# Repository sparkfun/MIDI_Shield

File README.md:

SparkFun MIDI Shield
====================

[*SparkFun MIDI Shield (DEV-12898)*](https://www.sparkfun.com/products/12898)

The MIDI Shield gives your Arduino access to the MIDI communication protocol, so you can control synthesizers, sequencers, and other musical devices.

Repository Contents
-------------------

* **/Firmware** - Example Arduino .ino sketch
* **/Hardware** - All Eagle design files (.brd, .sch)
* **/Production** - Production panel files (.brd)

Documentation
--------------
* **[Hookup Guide](https://learn.sparkfun.com/tutorials/midi-shield-hookup-guide?_ga=1.24780723.863167751.1453149924)** - Basic hookup guide for the MIDI Shield.
* **[SparkFun Fritzing repo](https://github.com/sparkfun/Fritzing_Parts)** - Fritzing diagrams for SparkFun products.
* **[SparkFun 3D Model repo](https://github.com/sparkfun/3D_Models)** - 3D models of SparkFun products. 
* **[SparkFun Graphical Datasheets](https://github.com/sparkfun/Graphical_Datasheets)** -Graphical Datasheets for various SparkFun products.

Product Versions
----------------
* [DEV-12898](https://www.sparkfun.com/products/12898)- Version 1.5. R3 compatible. Currently live. 
* [DEV-09595](https://www.sparkfun.com/products/retired/9595)- Version 1.3. Retired. 

Version History
---------------
* [V_1.5](https://github.com/sparkfun/MIDI_Shield/tree/V_1.5) - GitHub snapshot at V_1.5. 
* [V_1.3](https://github.com/sparkfun/MIDI_Shield/tree/v1.3) - GitHub snapshot at V_1.3

License Information
-------------------

This product is _**open source**_! 

Please review the LICENSE.md file for license information. 

If you have any questions or concerns on licensing, please contact techsupport@sparkfun.com.

Distributed as-is; no warranty is given.

\- Your friends at SparkFun.

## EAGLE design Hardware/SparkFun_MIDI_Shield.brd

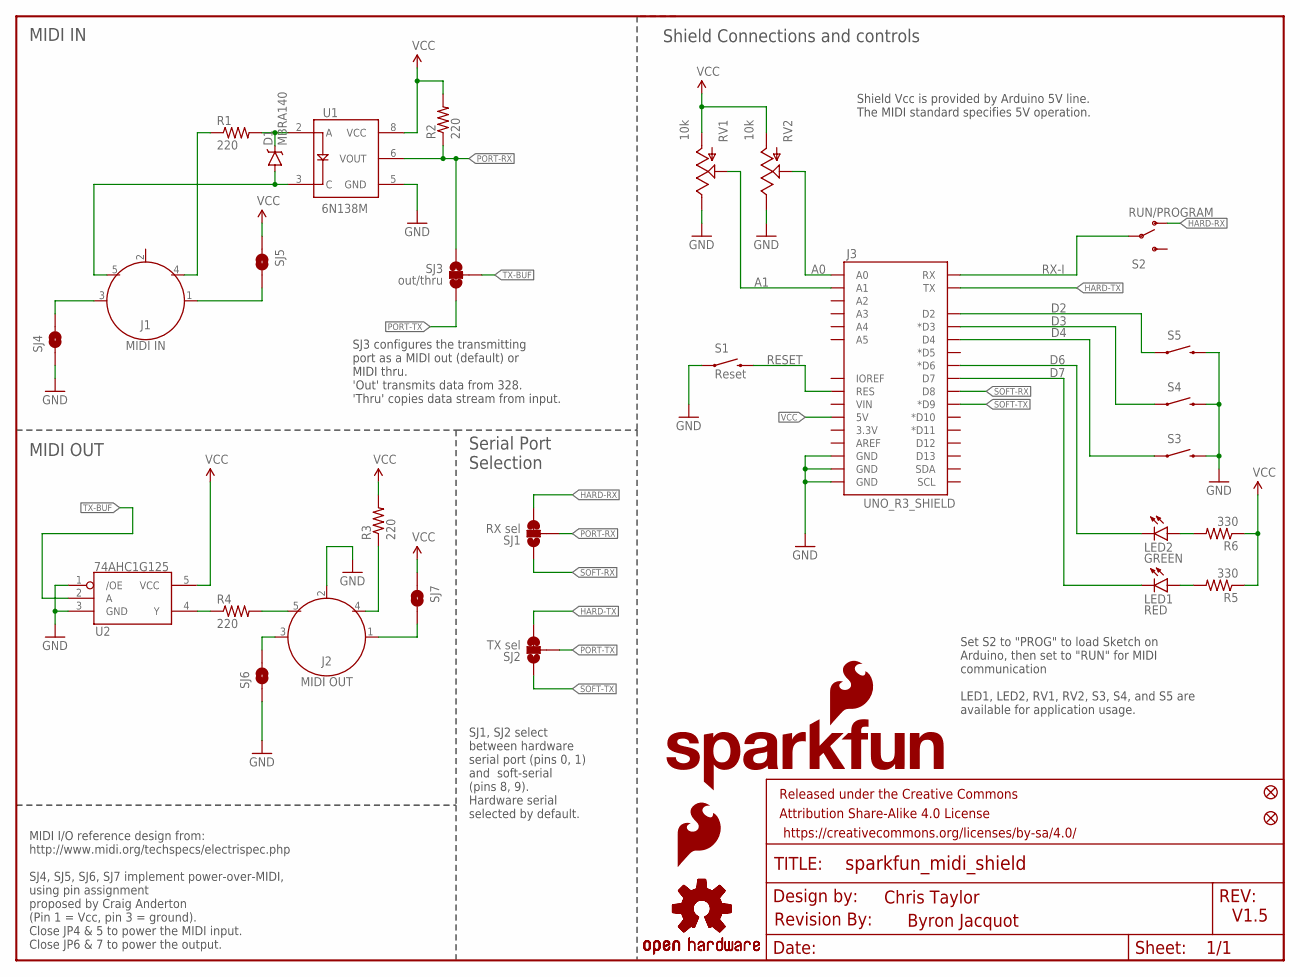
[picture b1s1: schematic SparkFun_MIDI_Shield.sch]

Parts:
D1: MBRA140; SMA-DIODE
FID1, FID2: FIDUCIALUFIDUCIAL; MICRO-FIDUCIAL
FRAME1: Frame; CREATIVE_COMMONS
J1: MIDI IN; 5-PIN-DIN-RA-PCB-NEW
J2: MIDI OUT; 5-PIN-DIN-RA-PCB-NEW
J3: UNO_R3_SHIELD
LED1: RED; LED-0603
LED2: GREEN; LED-0603
LOGO1: SFE_LOGO_NAME_FLAME.2_INCH; SFE_LOGO_NAME_FLAME_.2
LOGO2: OSHW-LOGOS; OSHW-LOGO-S
LOGO3: OSHW-LOGOM; OSHW-LOGO-M
LOGO5: SFE_LOGO_FLAME.1_INCH; SFE_LOGO_FLAME_.1
R1, R2, R3, R4: 220; 0603-RES
R5, R6: 330; 0603-RES
RV1, RV2: 10k; ALPS_POT
S1: Reset; TACTILE-SWITCH-SMD
S2: RUN/PROGRAM; AYZ0202
S3, S4, S5: SWITCH-MOMENTARY-212MM; TACTILE-PTH-12MM
SJ1: RX sel; PAD-JUMPER-3-2OF3_NC_BY_TRACE_YES_SILK_FULL_BOX
SJ2: TX sel; PAD-JUMPER-3-2OF3_NC_BY_TRACE_YES_SILK_FULL_BOX
SJ3: out/thru; PAD-JUMPER-3-2OF3_NC_BY_TRACE_YES_SILK_FULL_BOX
SJ4, SJ5, SJ6, SJ7: JUMPER-PAD-2-NOYES_SILK; PAD-JUMPER-2-NO_YES_SILK
U1: 6N138M; 8-SMD
U2: 74AHC1G125; SOT23-5
U$1: REVISION

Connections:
56: D1.C, R1.2, U1.2 (A)
1235: J2.4, R3.1
A0: J3.A0, RV2.P$2 (S)
A1: J3.A1, RV1.P$2 (S)
D2: J3.D2, S5.1
D3: J3.D3 (*D3), S4.1
D4: J3.D4, S3.1
D6: J3.D6 (*D6), LED2.C
D7: J3.D7, LED1.C
GND: J2.2, J3.GND@0 (GND), J3.GND@1 (GND), J3.GND@2 (GND), RV1.P$1 (E), RV2.P$1 (E), S1.1, S3.3 (2), S4.3 (2), S5.3 (2), SJ4.1, SJ6.1, U1.5 (GND), U2.1 (/OE), U2.3 (GND)
HARD-RX: S2.1 (O), SJ1.3
HARD-TX: J3.TX, SJ2.3
unnamed: J2.5, R4.2
unnamed: J1.4, R1.1
unnamed: R4.1, U2.4 (Y)
unnamed: J2.3, SJ6.2
unnamed: J2.1, SJ7.2
unnamed: J1.3, SJ4.2
unnamed: J1.1, SJ5.2
unnamed: LED1.A, R5.2
unnamed: LED2.A, R6.2
PIN5: D1.A, J1.5, U1.3 (C)
PORT-RX: R2.1, SJ1.2, SJ3.1, U1.6 (VOUT)
PORT-TX: SJ2.2, SJ3.3
RESET: J3.RES, S1.3 (2)
RX-I: J3.RX, S2.2
SOFT-RX: J3.D8, SJ1.1
SOFT-TX: J3.D9 (*D9), SJ2.1
TX-BUF: SJ3.2, U2.2 (A)
VCC: J3.5V, R2.2, R3.2, R5.1, R6.1, RV1.P$3 (A), RV2.P$3 (A), SJ5.1, SJ7.1, U1.8 (VCC), U2.5 (VCC)

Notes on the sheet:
MIDI IN
MIDI OUT
Byron Jacquot
V1.5
Shield Connections and controls
MIDI I/O reference design from: http://www.midi.org/techspecs/electrispec.php SJ4, SJ5, SJ6, SJ7 implement power-over-MIDI, using pin assignment proposed by Craig Anderton (Pin 1 = Vcc, pin 3 = ground). Close JP4 & 5 to power the MIDI input. Close JP6 & 7 to power the output.
Set S2 to "PROG" to load Sketch on Arduino, then set to "RUN" for MIDI communication LED1, LED2, RV1, RV2, S3, S4, and S5 are available for application usage.
Serial Port Selection
SJ1, SJ2 select between hardware serial port (pins 0, 1) and soft-serial (pins 8, 9). Hardware serial selected by default.
Shield Vcc is provided by Arduino 5V line. The MIDI standard specifies 5V operation.
SJ3 configures the transmitting port as a MIDI out (default) or MIDI thru. 'Out' transmits data from 328. 'Thru' copies data stream from input.
Chris Taylor

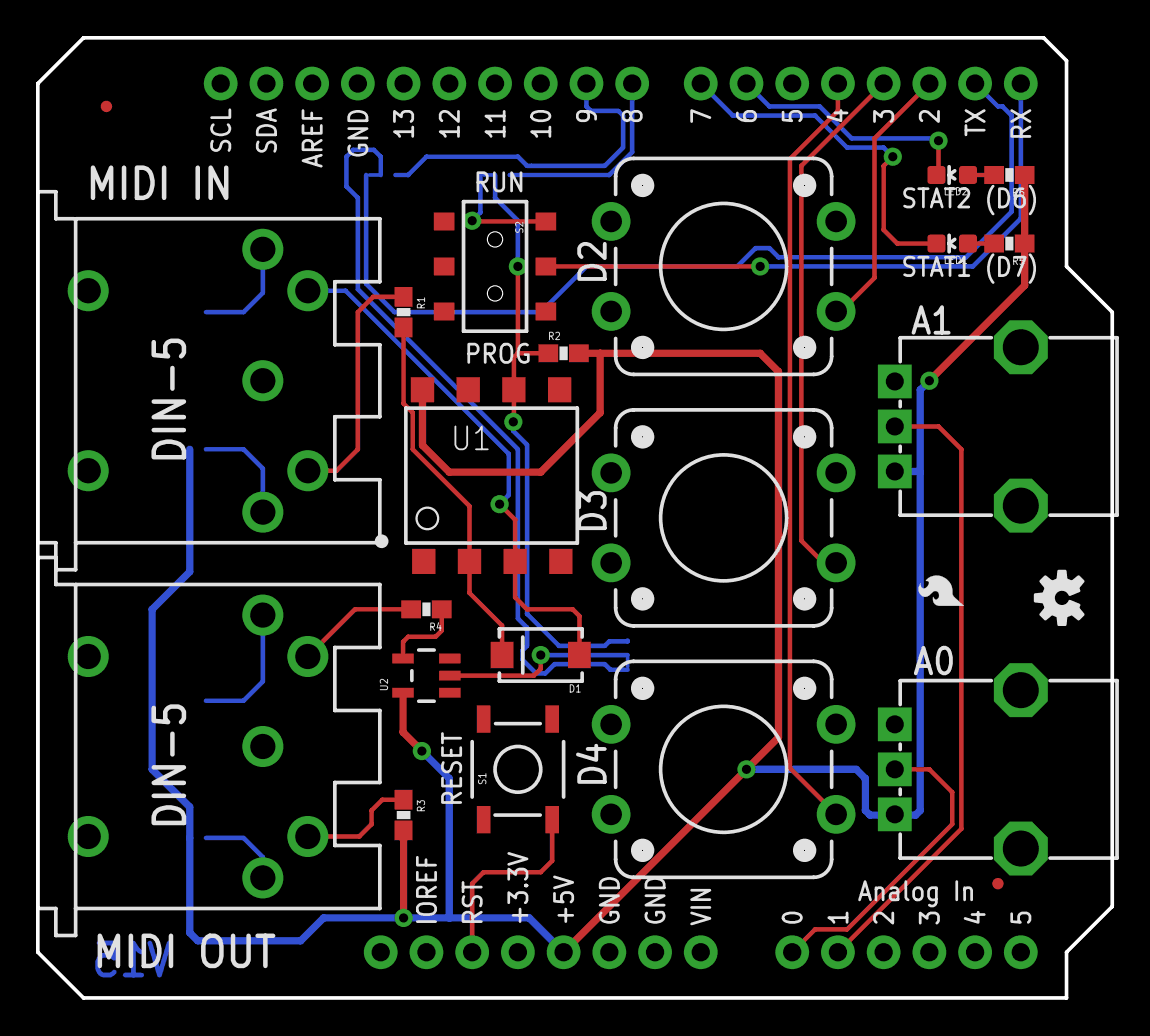
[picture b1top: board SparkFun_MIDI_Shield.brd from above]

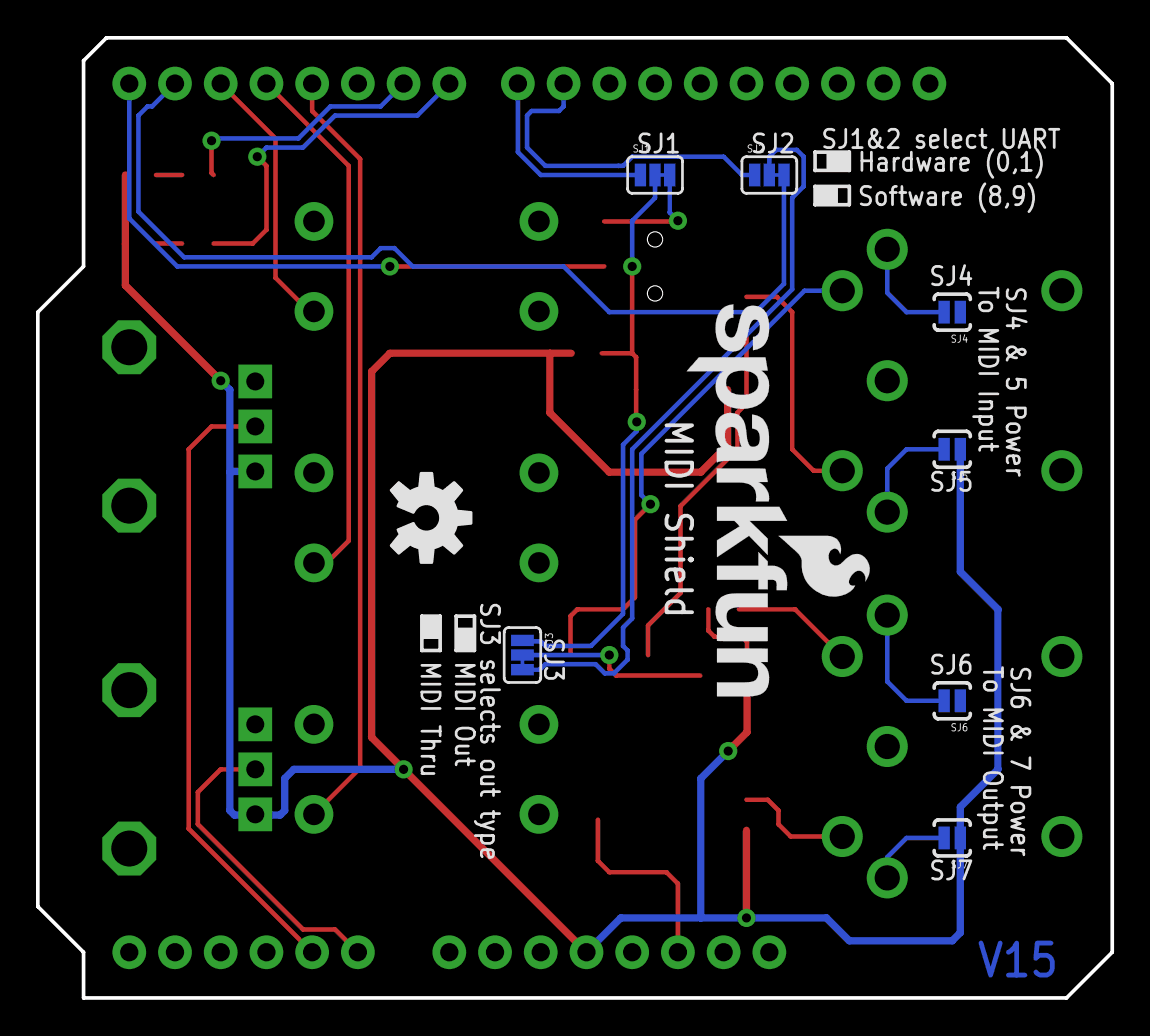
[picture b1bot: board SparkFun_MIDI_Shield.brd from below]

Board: 3 copper layers, 59.7 x 53.3 mm, 36 parts (9 on the bottom side), 30 nets.

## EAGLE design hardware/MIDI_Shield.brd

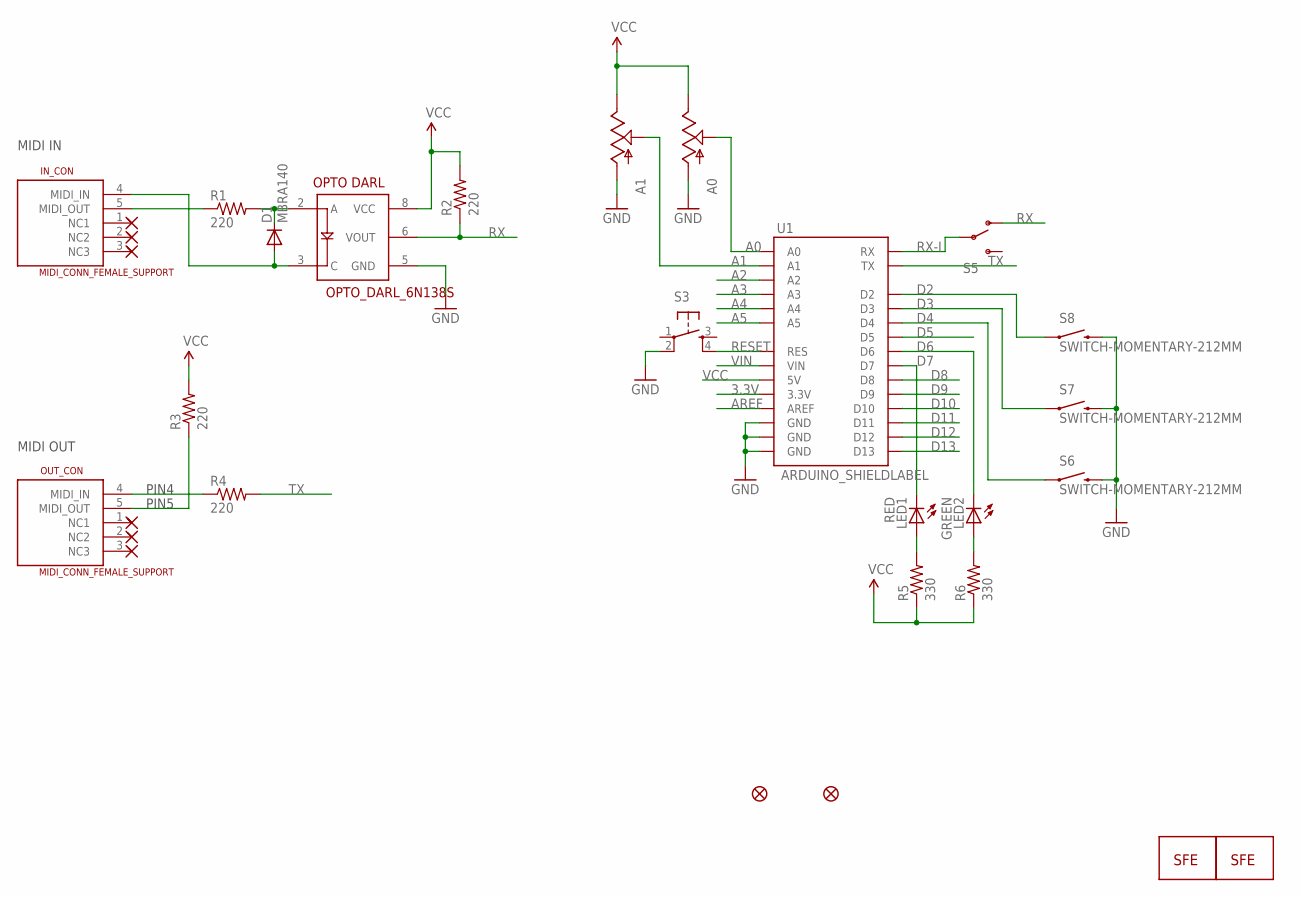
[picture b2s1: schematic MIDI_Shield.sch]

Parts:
A0, A1: POT; ALPS_POT
D1: MBRA140; SMA-DIODE
IN_CON: MIDI_CONN_FEMALE_SUPPORT; DIN_5_FEMALE_SUPPORT
JP1, JP2: FIDUCIALUFIDUCIAL; MICRO-FIDUCIAL
JP3: LOGO-SFENEW; SFE-NEW-WEBLOGO
JP4: LOGO-SFESK; SFE-LOGO-FLAME
LED1: RED; LED-0603
LED2: GREEN; LED-0603
OUT_CON: MIDI_CONN_FEMALE_SUPPORT; DIN_5_FEMALE_SUPPORT
R1, R2, R3, R4: 220; 0402-RES
R5, R6: 330; 0402-RES
S3: TAC_SWITCHSMD; TACTILE_SWITCH_SMD
S5: SWITCH-SPSTSMD; AYZ0202
S6, S7, S8: SWITCH-MOMENTARY-212MM; TACTILE-PTH-12MM
U1: ARDUINO_SHIELDLABEL; DUEMILANOVE_SHIELD
U$6: OPTO_DARL_6N138S; 8-SMD

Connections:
56: D1.C, R1.2, U$6.2 (A)
1235: OUT_CON.5 (MIDI_OUT), R3.1
A0: A0.P$2 (S), U1.A0; also elsewhere on the board
A1: A1.P$2 (S), U1.A1; also elsewhere on the board
D2: S8.1, U1.D2; also elsewhere on the board
D3: S7.1, U1.D3; also elsewhere on the board
D4: S6.1, U1.D4; also elsewhere on the board
D6: LED2.C, U1.D6; also elsewhere on the board
D7: LED1.C, U1.D7; also elsewhere on the board
GND: A0.P$3 (A), A1.P$3 (A), OUT_CON.2 (NC2), S3.2, S6.3 (2), S7.3 (2), S8.3 (2), U1.GND@0 (GND), U1.GND@1 (GND), U1.GND@2 (GND), U$6.5 (GND); also elsewhere on the board
unnamed: OUT_CON.4 (MIDI_IN), R4.1
unnamed: LED1.A, R5.2
unnamed: LED2.A, R6.2
unnamed: IN_CON.5 (MIDI_OUT), R1.1
PIN5: D1.A, IN_CON.4 (MIDI_IN), U$6.3 (C)
RX: R2.1, S5.1 (O), U$6.6 (VOUT)
RX-I: S5.2, U1.RX; also elsewhere on the board
TX: R4.2, U1.TX; also elsewhere on the board

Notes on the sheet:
PIN4
PIN5
MIDI IN
MIDI OUT

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
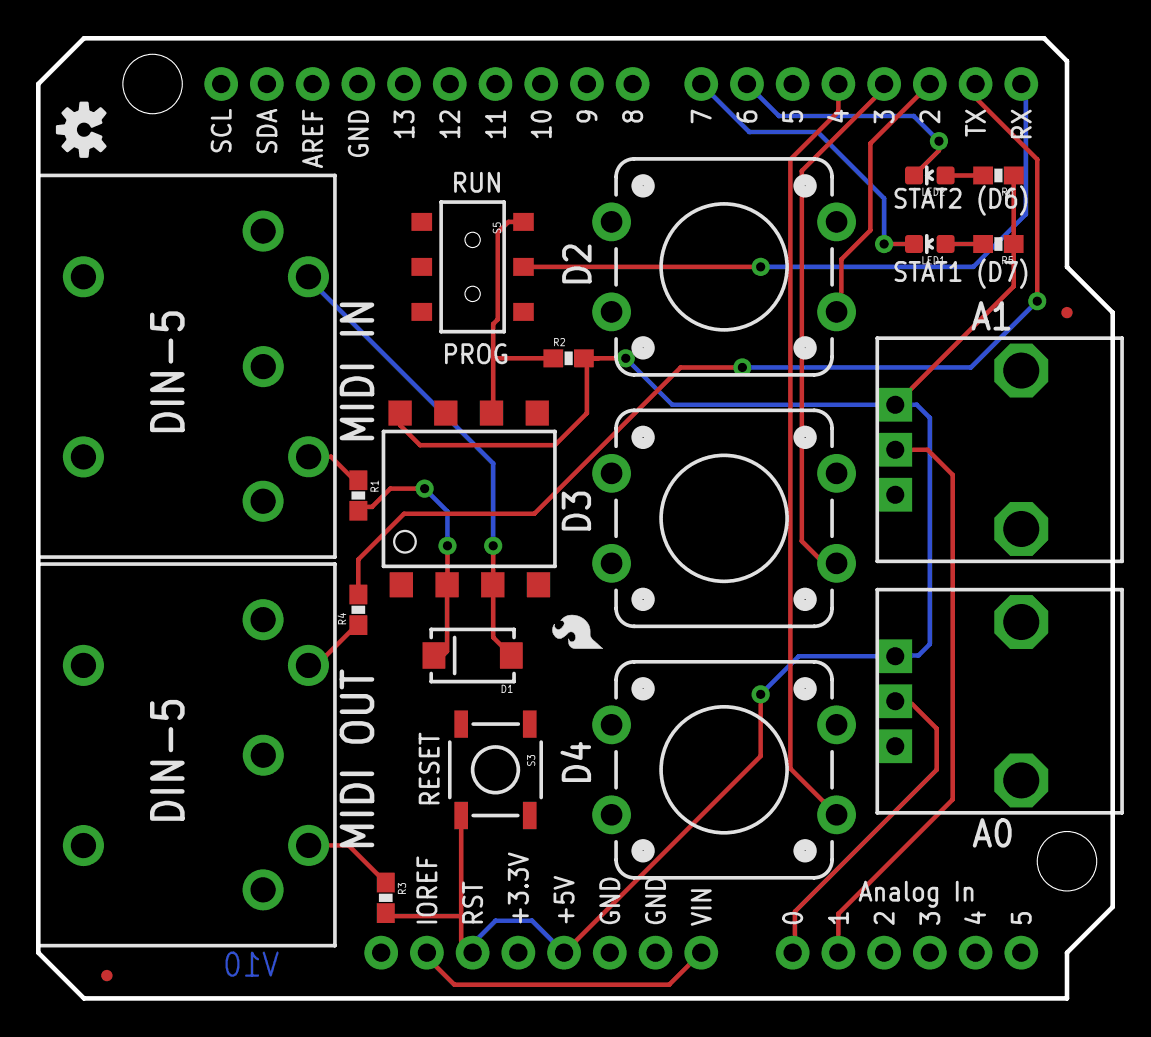
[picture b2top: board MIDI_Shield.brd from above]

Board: 2 copper layers, 59.7 x 53.3 mm, 27 parts (1 on the bottom side), 20 nets.

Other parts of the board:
U$1: ARDUINO_R3_SHIELD; UNO_R3_SHIELD
U$2, U$3: STAND-OFF
U$4: OSHW-LOGO-S

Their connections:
A0: U$1.A0; also elsewhere on the board
A1: U$1.A1; also elsewhere on the board
D2: U$1.D2; also elsewhere on the board
D3: U$1.D3; also elsewhere on the board
D4: U$1.D4; also elsewhere on the board
D6: U$1.D6; also elsewhere on the board
D7: U$1.D7; also elsewhere on the board
GND: U$1.GND@0, U$1.GND@1, U$1.GND@2; also elsewhere on the board
RX-I: U$1.RX; also elsewhere on the board
TX: U$1.TX; also elsewhere on the board
VIN: U$1.IOREF, U$1.VIN

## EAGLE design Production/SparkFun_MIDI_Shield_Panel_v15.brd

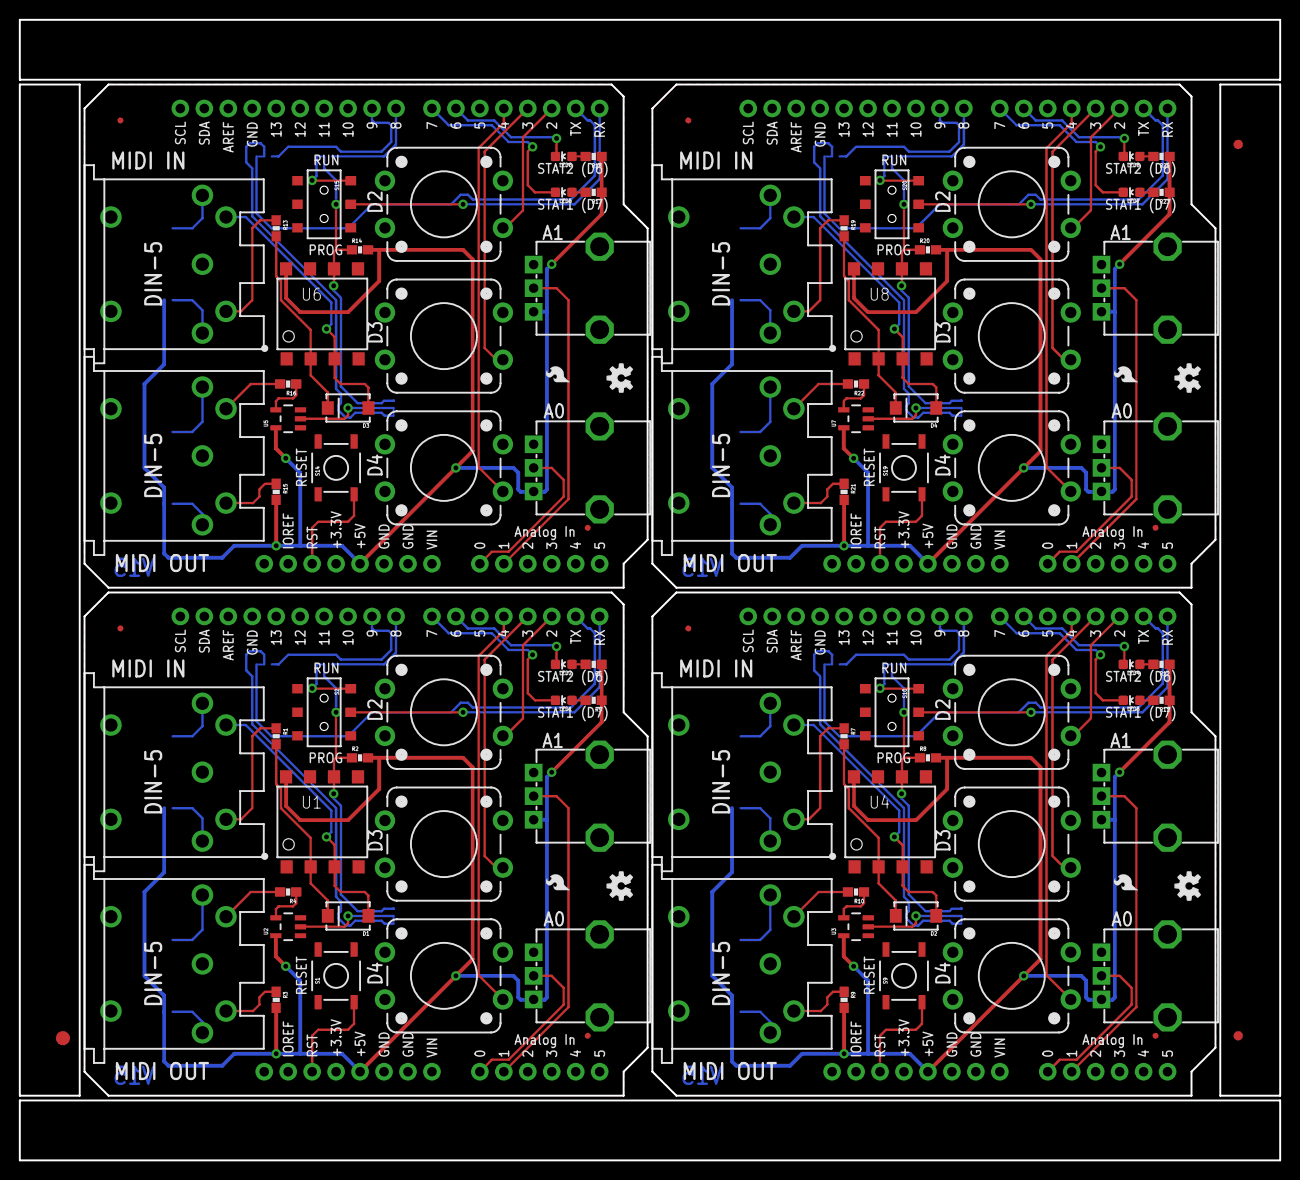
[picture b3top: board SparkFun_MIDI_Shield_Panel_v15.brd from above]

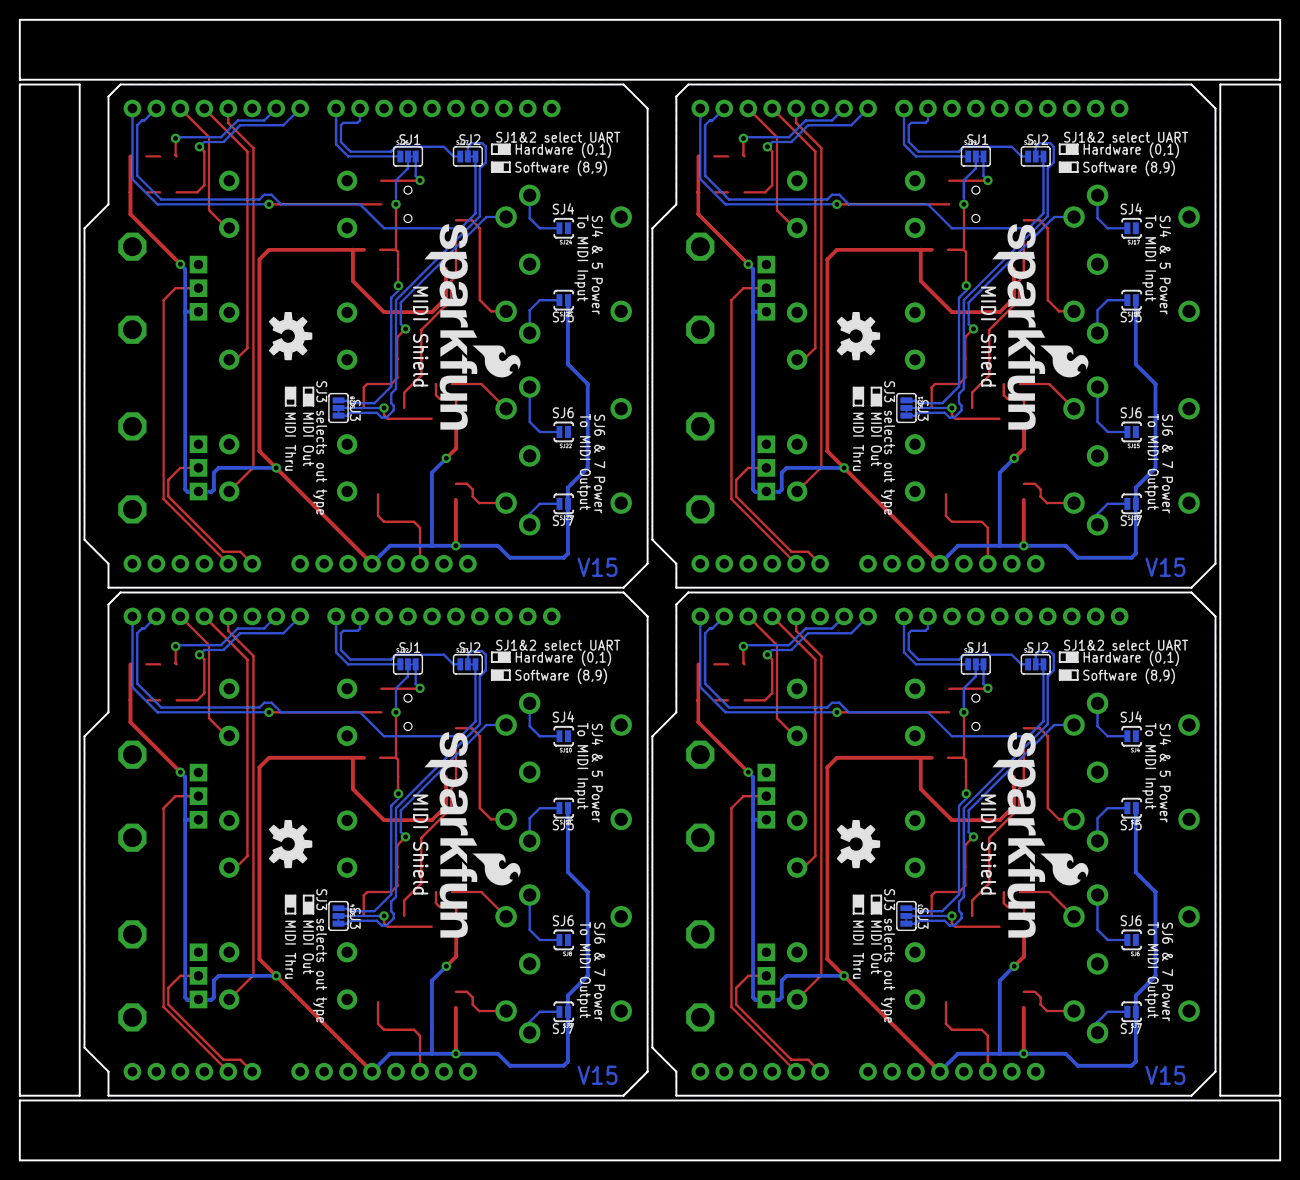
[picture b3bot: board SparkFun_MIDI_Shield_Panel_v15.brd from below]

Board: 3 copper layers, 133.6 x 120.9 mm, 139 parts (36 on the bottom side), 120 nets.

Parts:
D1, D2, D3, D4: MBRA140; SMA-DIODE
E$1: FIDUCIAL-1.5X3
E$4, E$5: FIDUCIAL-1X2
FID1, FID2, FID3, FID4, FID5, FID6, FID7, FID8: FIDUCIALUFIDUCIAL; MICRO-FIDUCIAL
J1, J4, J7, J10: MIDI IN; 5-PIN-DIN-RA-PCB-NEW
J2, J5, J8, J11: MIDI OUT; 5-PIN-DIN-RA-PCB-NEW
J3, J6, J9, J12: UNO_R3_SHIELD
LED1, LED3, LED5, LED7: RED; LED-0603
LED2, LED4, LED6, LED8: GREEN; LED-0603
LOGO1, LOGO4, LOGO9, LOGO13: SFE_LOGO_NAME_FLAME.2_INCH; SFE_LOGO_NAME_FLAME_.2
LOGO2, LOGO6, LOGO10, LOGO14: OSHW-LOGOS; OSHW-LOGO-S
LOGO3, LOGO7, LOGO11, LOGO15: OSHW-LOGOM; OSHW-LOGO-M
LOGO5, LOGO8, LOGO12, LOGO16: SFE_LOGO_FLAME.1_INCH; SFE_LOGO_FLAME_.1
R1, R2, R3, R4, R7, R8, R9, R10, R13, R14, R15, R16, R19, R20, R21, R22: 220; 0603-RES
R5, R6, R11, R12, R17, R18, R23, R24: 330; 0603-RES
RV1, RV2, RV3, RV4, RV5, RV6, RV7, RV8: 10k; ALPS_POT
S1, S9, S14, S19: Reset; TACTILE-SWITCH-SMD
S2, S10, S15, S20: RUN/PROGRAM; AYZ0202
S3, S4, S5, S6, S7, S8, S11, S12, S13, S16, S17, S18: SWITCH-MOMENTARY-212MM; TACTILE-PTH-12MM
SJ1, SJ12, SJ19, SJ26: RX sel; PAD-JUMPER-3-2OF3_NC_BY_TRACE_YES_SILK_FULL_BOX
SJ2, SJ13, SJ20, SJ27: TX sel; PAD-JUMPER-3-2OF3_NC_BY_TRACE_YES_SILK_FULL_BOX
SJ3, SJ14, SJ21, SJ28: out/thru; PAD-JUMPER-3-2OF3_NC_BY_TRACE_YES_SILK_FULL_BOX
SJ4, SJ5, SJ6, SJ7, SJ8, SJ9, SJ10, SJ11, SJ15, SJ16, SJ17, SJ18, SJ22, SJ23, SJ24, SJ25: JUMPER-PAD-2-NOYES_SILK; PAD-JUMPER-2-NO_YES_SILK
U1, U4, U6, U8: 6N138M; 8-SMD
U2, U3, U5, U7: 74AHC1G125; SOT23-5

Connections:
1: D2.C, R7.2, U4.2
2: J5.4, R9.1
3: D3.C, R13.2, U6.2
4: J8.4, R15.1
5: D4.C, R19.2, U8.2
6: J11.4, R21.1
56: D1.C, R1.2, U1.2
1235: J2.4, R3.1
A0: J3.A0, RV2.P$2
A1: J3.A1, RV1.P$2
A2: J6.A1, RV3.P$2
A3: J6.A0, RV4.P$2
A4: J9.A1, RV5.P$2
A5: J9.A0, RV6.P$2
A6: J12.A1, RV7.P$2
A7: J12.A0, RV8.P$2
D1: J6.D2, S8.1
D2: J3.D2, S5.1
D3: J3.D3, S4.1
D4: J3.D4, S3.1
D5: J6.D3, S7.1
D6: J3.D6, LED2.C
D7: J3.D7, LED1.C
D8: J6.D4, S6.1
D9: J6.D7, LED3.C
D10: J6.D6, LED4.C
D11: J9.D2, S13.1
D12: J9.D3, S12.1
D13: J9.D4, S11.1
D14: J9.D7, LED5.C
D15: J9.D6, LED6.C
D16: J12.D2, S18.1
D17: J12.D3, S17.1
D18: J12.D4, S16.1
D19: J12.D7, LED7.C
D20: J12.D6, LED8.C
GND: J2.2, J3.GND@0, J3.GND@1, J3.GND@2, RV1.P$1, RV2.P$1, S1.1, S3.3, S4.3, S5.3, SJ4.1, SJ6.1, U1.5, U2.1, U2.3
GND1: J5.2, J6.GND@0, J6.GND@1, J6.GND@2, RV3.P$1, RV4.P$1, S6.3, S7.3, S8.3, S9.1, SJ8.1, SJ10.1, U3.1, U3.3, U4.5
GND2: J8.2, J9.GND@0, J9.GND@1, J9.GND@2, RV5.P$1, RV6.P$1, S11.3, S12.3, S13.3, S14.1, SJ15.1, SJ17.1, U5.1, U5.3, U6.5
GND3: J11.2, J12.GND@0, J12.GND@1, J12.GND@2, RV7.P$1, RV8.P$1, S16.3, S17.3, S18.3, S19.1, SJ22.1, SJ24.1, U7.1, U7.3, U8.5
HARD-RX: S2.1, SJ1.3
HARD-RX1: S10.1, SJ12.3
HARD-RX2: S15.1, SJ19.3
HARD-RX3: S20.1, SJ26.3
HARD-TX: J3.TX, SJ2.3
HARD-TX1: J6.TX, SJ13.3
HARD-TX2: J9.TX, SJ20.3
HARD-TX3: J12.TX, SJ27.3
unnamed: J2.5, R4.2
unnamed: J1.4, R1.1
unnamed: R4.1, U2.4
unnamed: J2.3, SJ6.2
unnamed: J2.1, SJ7.2
unnamed: J1.3, SJ4.2
unnamed: J1.1, SJ5.2
unnamed: LED3.A, R11.2
unnamed: LED1.A, R5.2
unnamed: LED2.A, R6.2
unnamed: LED4.A, R12.2
unnamed: J4.4, R7.1
unnamed: J5.5, R10.2
unnamed: R10.1, U3.4
unnamed: J5.3, SJ8.2
unnamed: J5.1, SJ9.2
unnamed: J4.3, SJ10.2
unnamed: J4.1, SJ11.2
unnamed: LED5.A, R17.2
unnamed: LED6.A, R18.2
unnamed: J7.4, R13.1
unnamed: J8.5, R16.2
unnamed: R16.1, U5.4
unnamed: J8.3, SJ15.2
unnamed: J8.1, SJ16.2
unnamed: J7.3, SJ17.2
unnamed: J7.1, SJ18.2
unnamed: LED7.A, R23.2
unnamed: LED8.A, R24.2
unnamed: J10.4, R19.1
unnamed: J11.5, R22.2
unnamed: R22.1, U7.4
unnamed: J11.3, SJ22.2
unnamed: J11.1, SJ23.2
unnamed: J10.3, SJ24.2
unnamed: J10.1, SJ25.2
PIN1: D2.A, J4.5, U4.3
PIN2: D3.A, J7.5, U6.3
PIN3: D4.A, J10.5, U8.3
PIN5: D1.A, J1.5, U1.3
PORT-RX: R2.1, SJ1.2, SJ3.1, U1.6
PORT-RX1: R8.1, SJ12.2, SJ14.1, U4.6
PORT-RX2: R14.1, SJ19.2, SJ21.1, U6.6
PORT-RX3: R20.1, SJ26.2, SJ28.1, U8.6
PORT-TX: SJ2.2, SJ3.3
PORT-TX1: SJ13.2, SJ14.3
PORT-TX2: SJ20.2, SJ21.3
PORT-TX3: SJ27.2, SJ28.3
RESET: J3.RES, S1.3
RESET1: J6.RES, S9.3
RESET2: J9.RES, S14.3
RESET3: J12.RES, S19.3
RX-I: J3.RX, S2.2
RX-I1: J6.RX, S10.2
RX-I2: J9.RX, S15.2
RX-I3: J12.RX, S20.2
SOFT-RX: J3.D8, SJ1.1
SOFT-RX1: J6.D8, SJ12.1
SOFT-RX2: J9.D8, SJ19.1
SOFT-RX3: J12.D8, SJ26.1
SOFT-TX: J3.D9, SJ2.1
SOFT-TX1: J6.D9, SJ13.1
SOFT-TX2: J9.D9, SJ20.1
SOFT-TX3: J12.D9, SJ27.1
TX-BUF: SJ3.2, U2.2
TX-BUF1: SJ14.2, U3.2
TX-BUF2: SJ21.2, U5.2
TX-BUF3: SJ28.2, U7.2
VCC: J3.5V, R2.2, R3.2, R5.1, R6.1, RV1.P$3, RV2.P$3, SJ5.1, SJ7.1, U1.8, U2.5
VCC1: J6.5V, R8.2, R9.2, R11.1, R12.1, RV3.P$3, RV4.P$3, SJ9.1, SJ11.1, U3.5, U4.8
VCC2: J9.5V, R14.2, R15.2, R17.1, R18.1, RV5.P$3, RV6.P$3, SJ16.1, SJ18.1, U5.5, U6.8
VCC3: J12.5V, R20.2, R21.2, R23.1, R24.1, RV7.P$3, RV8.P$3, SJ23.1, SJ25.1, U7.5, U8.8

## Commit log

2014-04-29 Initial Commit with Brd/Sch Files
2014-05-19 Added pin 2 ground, 0603, oshw, v#, trace/sch rework
2015-01-19 Adding in Firmware and board files
2015-01-19 Updating to current board files
2015-02-13 Updating to V1.5.
    0603 footprints.
    R3 shield footprint.
    Redrew MIDI connectors to match physical parts.
    Added optional jumpers for power-over-midi.
    General component updates, PROD_IDs and cleanup.
2015-02-16 Updates after engineering review.
    Added jumper to allow optional soft serial.
2015-02-17 Updates after QC checklist.
2015-02-17 Fixed 3 way junction net near LEDs
    Just cleaning up 3 way net junction on VCC side of LEDs
2015-06-03 Prototype Revisions WIP
2015-06-04 WIP Mostly complete.
    Proto issues handles.
    -Pots turn the right way.
    -Option for out vs thru.
    -JP/SJ terminology resolved.
    -More clearance around new connector component.
2015-06-05 Board updates.
    Small tweaks before submission for review.
2015-06-05 Small text change
    Fixing capitalization...really a change to get my renamed branch pushed
    (V_1.5 -> V_1.6).
2015-06-08 Updates based on QC checklist.
    -Measures layer populated.
    -U1 got name/value.
    -Added stubs to some parts on schem.
    -Version # back to 1.5.
2015-06-24 Fixing resistor obscured by output connector.
2015-08-03 Adding MIDI-sniffer sketch
    Mostly complete.
    Sysex might be a little rough/incomplete.
2015-08-03 Fixing QC review issue with LP1,2 naming.
    TX & RX were transposed in jumper names.
2015-08-04 created panel v15
2015-09-04 Adding a raw-hex mode.
    Sniffer ordinarily uses the output of the 47 Effects MIDI library, which
    handles all of the tricky stuff within MIDI.
    If you hold the D2 button, it switches to a raw hex display. This is
    useful for tracking down problems with running status, incomplete
    messages, etc.
2015-09-17 Incorporating test & demo sketches.
2015-09-21 Adding continue functionality
    It'll remember clock ticks when stopped, and restore them if it receives
    a continue message.
2015-09-25 Some reformatting.
    Clock-gen was in a double nested directory
    (clock-gen/clock-gen/clock-gen.ino) - fixed.
    Added MIDI-2-CV & DAC integration test.
2015-10-02 Updating MIDI-CV example.
    Added license.
    Implemented arpeggiator modes & improved note tracking object.
2015-10-05 Added sustain pedal to arpeggiator.
    Messy work in progress.
2015-10-05 Note tracking is now cleaner.
    Refactored into two separate classes.
2015-10-06 Adding comments and cleaning up further.
2015-10-08 Re-orgasnizing code for release.
    Removed old sample.
    Added boilerplate & license references to all examples.
    Defaulted most examples to use hardware serial (except the sniffer,
    which need hardware serial to print).
2015-10-12 Updating README
2015-10-13 Removing some debug statements from "Verbose" macro.
2016-01-21 Added Documentation
2016-01-21 Added product name to readme doc
2019-10-14 Update README.md
    escaped the bullet point at the end to make it a hyphen as intended

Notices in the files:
parts and their libraries:
SparkFun-Aesthetics: Licensing: Creative Commons ShareAlike 4.0 International - https://creativecommons.org/licenses/by-sa/4.0
SparkFun-Aesthetics: Released under the Creative Commons Attribution Share-Alike 4.0 License
SparkFun-Aesthetics: https://creativecommons.org/licenses/by-sa/4.0
